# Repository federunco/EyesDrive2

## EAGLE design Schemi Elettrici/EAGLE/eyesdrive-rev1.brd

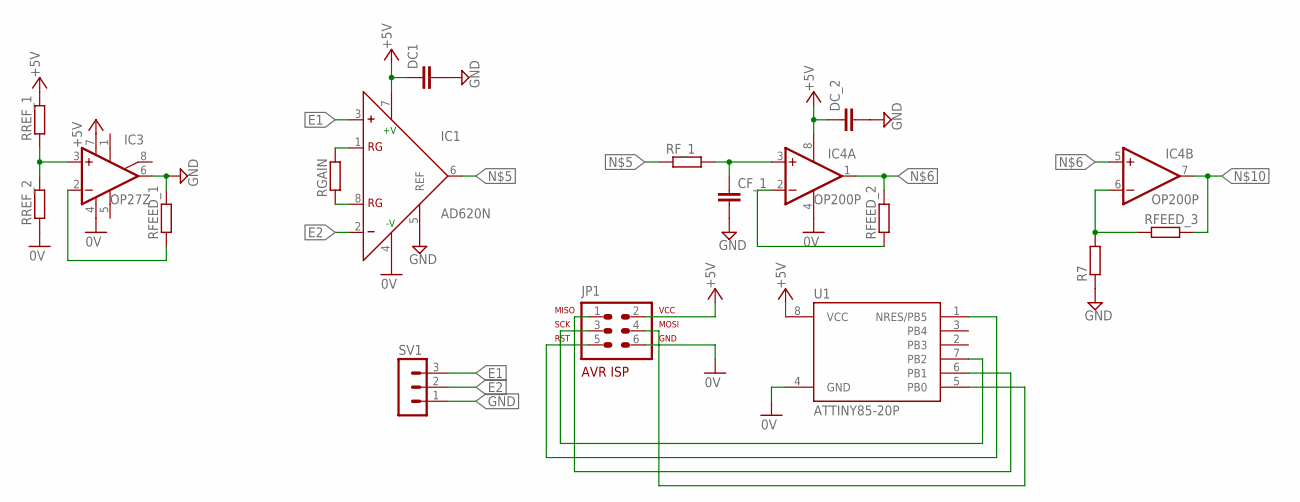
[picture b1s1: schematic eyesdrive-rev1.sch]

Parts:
CF_1: C-EU025-025X050; C025-025X050
DC1: C-EU050-025X075; C050-025X075
DC_2: C-EU025-025X050; C025-025X050
IC1: AD620N; DIL08
IC3: OP27Z; DIL08
IC4: OP200P; DIL08
JP1: AVR-ISP-6VERT; AVR-ISP-6
R7: R-EU_0207/7; 0207/7
RFEED_1, RFEED_2, RFEED_3: R-EU_0207/7; 0207/7
RF_1: R-EU_0207/7; 0207/7
RGAIN: R-EU_0207/7; 0207/7
RREF_1, RREF_2: R-EU_0207/7; 0207/7
SV1: MA03-1
U1: ATTINY85-20P; PDIP08_300MIL

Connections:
0V: IC1.4 (-V), IC3.4 (V-), IC4.4 (V-), JP1.6, RREF_2.1, U1.4 (GND)
+5V: DC1.1, DC_2.1, IC1.7 (+V), IC3.7 (V+), IC4.8 (V+), JP1.2, RREF_1.2, U1.8 (VCC)
E1: IC1.3 (+), SV1.3
E2: IC1.2 (-), SV1.2
GND: CF_1.2, DC1.2, DC_2.2, IC1.5 (REF), IC3.6 (OUT), R7.1, RFEED_1.2, SV1.1
unnamed: IC1.1 (RG), RGAIN.2
unnamed: IC3.3 (+IN), RREF_1.1, RREF_2.2
unnamed: IC3.2 (-IN), RFEED_1.1
unnamed: IC1.8 (RG), RGAIN.1
unnamed: IC1.6 (OUT), RF_1.1
unnamed: IC4.1 (OUT), IC4.5 (+IN), RFEED_2.2
unnamed: IC4.2 (-IN), RFEED_2.1
unnamed: CF_1.1, IC4.3 (+IN), RF_1.2
unnamed: IC4.6 (-IN), R7.2, RFEED_3.1
unnamed: IC4.7 (OUT), RFEED_3.2
unnamed: JP1.3, U1.7 (PB2)
unnamed: JP1.5, U1.1 (NRES/PB5)
unnamed: JP1.1, U1.6 (PB1)
unnamed: JP1.4, U1.5 (PB0)

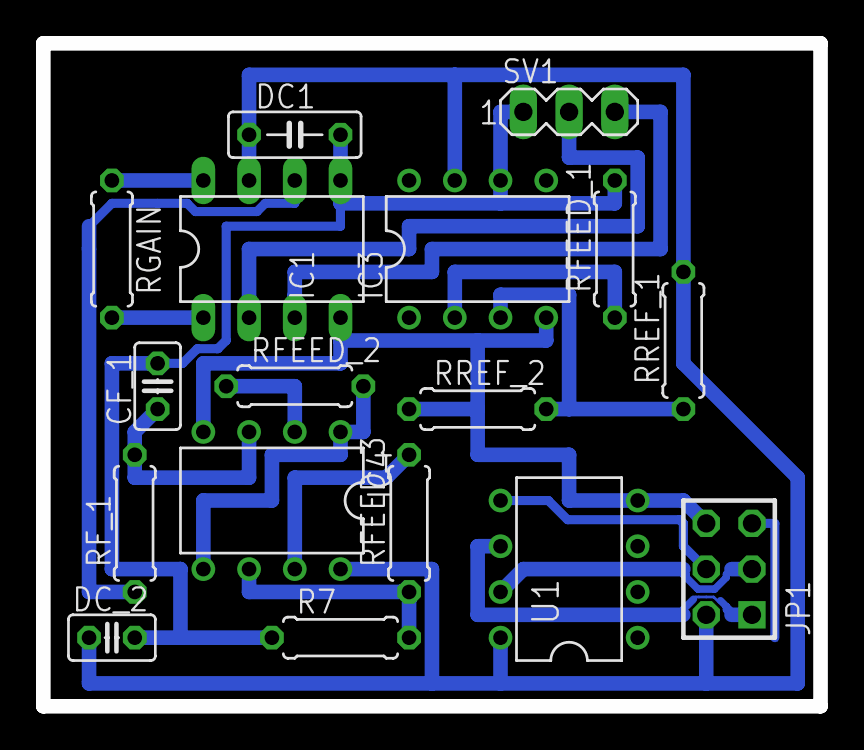
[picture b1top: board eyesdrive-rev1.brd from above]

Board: 2 copper layers, 43.2 x 36.8 mm, 17 parts (0 on the bottom side), 19 nets.

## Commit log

2019-06-17 Commit iniziale, caricamento documentazione frontend
2019-06-18 Aggiunte specifiche protocollo ED2P + codice di test
2019-06-18 Implementazione iniziale del protocollo sul firmware frontend
